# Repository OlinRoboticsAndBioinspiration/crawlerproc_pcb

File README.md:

crawlerproc-pcb
===============

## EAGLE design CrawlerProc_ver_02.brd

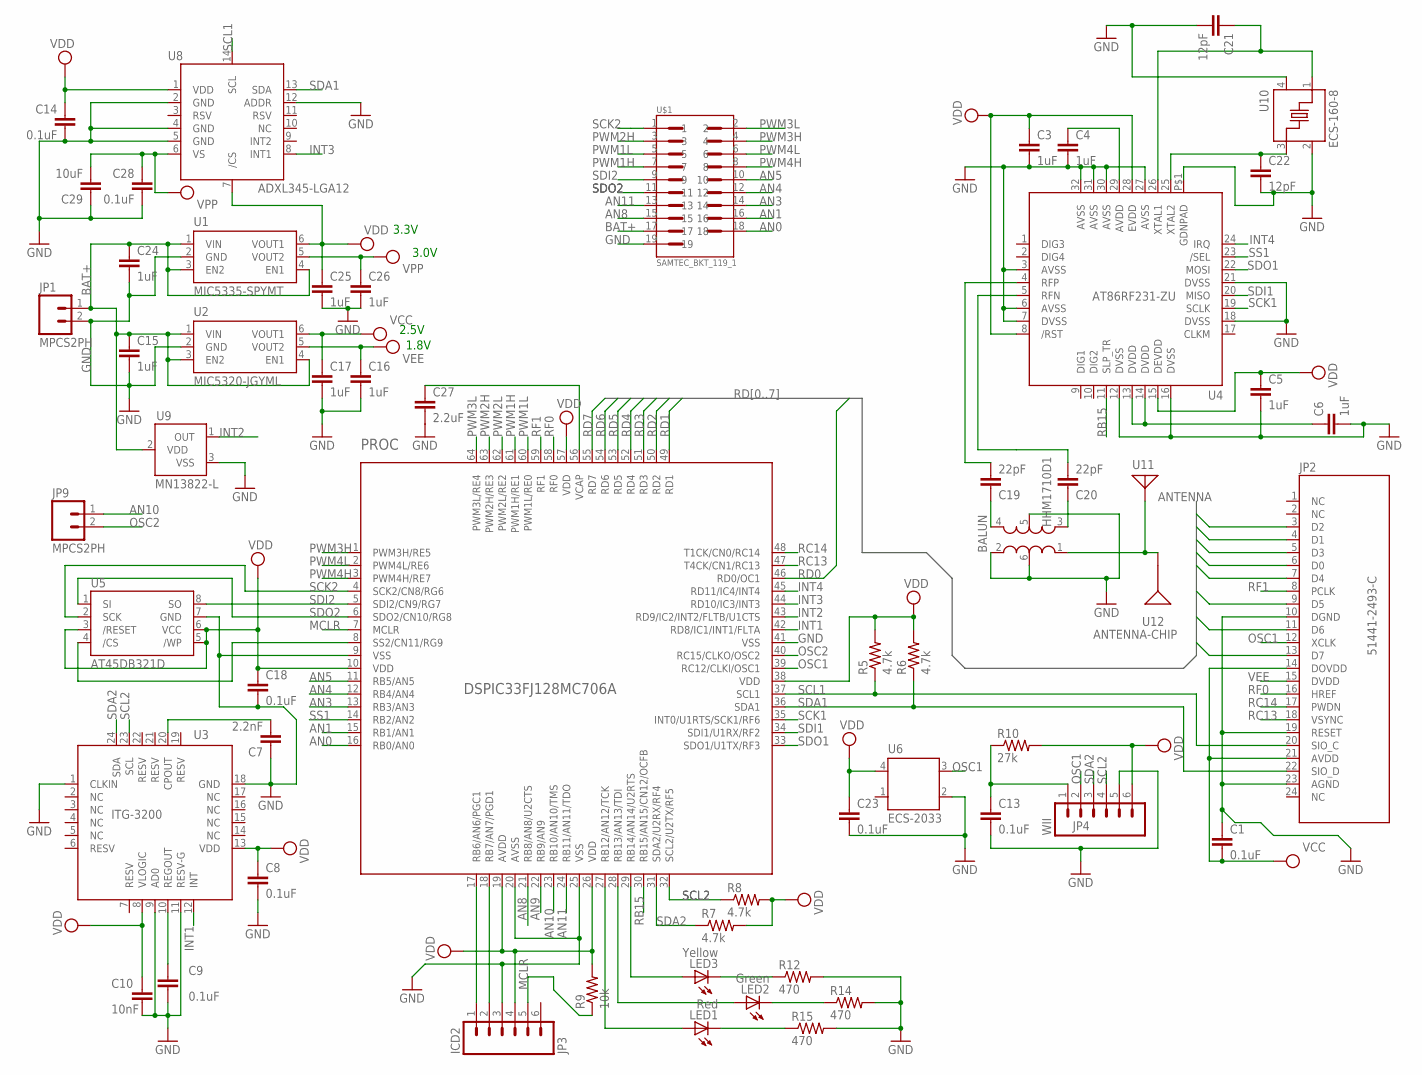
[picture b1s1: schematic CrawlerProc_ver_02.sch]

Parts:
BALUN: HHM1710D1; BALUN
C1, C8, C9, C13, C14, C18, C23, C28: 0.1uF; 0402-CAP
C3, C4, C5, C6, C15, C16, C17, C24, C25, C26: 1uF; 0402-CAP
C7: 2.2nF; 0402-CAP
C10: 10nF; 0402-CAP
C19, C20: 22pF; 0402-CAP
C21, C22: 12pF; 0402-CAP
C27: 2.2uF; 0402-CAP
C29: 10uF; 0603-CAP
JP1, JP9: MPCS2PH; MOLEX-PICO_CLASP_S2P
JP2: 51441-2493-C; MOLEX-52740-2490
JP3: ICD2; MOLEX-PICO_CLASP_S6P
JP4: WII; MOLEX-PICO_CLASP_S6P
LED1: Red; CHIP-LED0603
LED2: Green; CHIP-LED0603
LED3: Yellow; CHIP-LED0603
PROC: DSPIC33FJ128MC706A; TQFP64
R5, R6, R7, R8: 4.7k; R0402
R9: 10k; R0402
R10: 27k; R0402
R12, R14, R15: 470; R0402
U1: MIC5335-SPYMT; MLF-6
U2: MIC5320-JGYML; MLF-6
U3: ITG-3200; QFN-24
U4: AT86RF231-ZU; QFN-32
U5: AT45DB321D; MLF(VDFN)-8
U6: ECS-2033; OSCILLATOR-SMD
U8: ADXL345-LGA12; LGA14
U9: MN13822-L; SOT-23-3
U10: ECS-160-8; CRYSTAL-SMD
U11: ANTENNA; ANTENNA_PAD
U12: ANTENNA-CHIP
U$1: SAMTEC_BKT_119_1; SAMTEC_19P_1MM_MICRO_CONN

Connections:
AN0: PROC.16 (RB0/AN0), U$1.18
AN1: PROC.15 (RB1/AN1), U$1.16
AN3: PROC.13 (RB3/AN3), U$1.14
AN4: PROC.12 (RB4/AN4), U$1.12
AN5: PROC.11 (RB5/AN5), U$1.10
AN8: PROC.21 (RB8/AN8/U2CTS), U$1.15
AN9: PROC.22 (RB9/AN9)
AN10: JP9.1, PROC.23 (RB10/AN10/TMS)
AN11: PROC.24 (RB11/AN11/TDO), U$1.13
BAT+: C15.1, C24.1, JP1.1, U1.1 (VIN), U1.3 (EN2), U1.4 (EN1), U2.1 (VIN), U2.3 (EN2), U2.4 (EN1), U9.2 (VDD), U$1.17
GND: BALUN.2 (RFGND), BALUN.5 (GND), BALUN.6 (NC), C1.1, C3.2, C4.2, C5.2, C6.2, C7.1, C8.2, C9.2, C10.2, C13.2, C14.2, C15.2, C16.2, C17.2, C18.2, C21.2, C22.2, C23.2, C24.2, C25.2, C26.2, C27.2, C28.2, C29.1, JP1.2, JP2.10 (DGND), JP2.19 (RESET), JP2.23 (AGND), JP3.3, JP4.5, PROC.9 (VSS), PROC.20 (AVSS), PROC.25 (VSS), PROC.41 (VSS), R12.2, R14.2, R15.2, U1.2 (GND), U2.2 (GND), U3.1 (CLKIN), U3.9 (AD0), U3.11 (RESV-G), U3.18 (GND), U4.3 (AVSS), U4.6 (AVSS), U4.7 (DVSS), U4.12 (DVSS), U4.16 (DVSS), U4.18 (DVSS), U4.21 (DVSS), U4.27 (AVSS), U4.30 (AVSS), U4.31 (AVSS), U4.32 (AVSS), U4.P$1 (GDNPAD), U5.7 (GND), U6.2 (GND), U8.2 (GND), U8.4 (GND), U8.5 (GND), U8.12 (ADDR), U9.3 (VSS), U10.2 (GND), U10.4 (GND), U$1.19
INT1: PROC.42 (RD8/IC1/INT1/FLTA), U3.12 (INT)
INT2: PROC.43 (RD9/IC2/INT2/FLTB/U1CTS), U9.1 (OUT)
INT3: PROC.44 (RD10/IC3/INT3), U8.8 (INT1)
INT4: PROC.45 (RD11/IC4/INT4), U4.24 (IRQ)
MCLR: JP3.5, PROC.7 (MCLR), R9.1
unnamed: C27.1, PROC.56 (VCAP)
unnamed: LED3.C, R12.1
unnamed: LED3.A, PROC.29 (RB14/AN14/U2RTS)
unnamed: LED2.C, R14.1
unnamed: LED1.C, R15.1
unnamed: LED2.A, PROC.28 (RB13/AN13/TDI)
unnamed: LED1.A, PROC.27 (RB12/AN12/TCK)
unnamed: JP3.1, PROC.17 (RB6/AN6/PGC1)
unnamed: C4.1, U4.29 (AVDD)
unnamed: JP3.2, PROC.18 (RB7/AN7/PGD1)
unnamed: C6.1, U4.13 (DVDD), U4.14 (DVDD)
unnamed: C7.2, U3.20 (CPOUT)
unnamed: C9.1, U3.10 (REGOUT)
unnamed: BALUN.4 (BAL4), C19.1
unnamed: BALUN.3 (BAL3), C20.1
unnamed: C19.2, U4.4 (RFP)
unnamed: PROC.8 (SS2/CN11/RG9), U5.4 (/CS)
unnamed: C20.2, U4.5 (RFN)
unnamed: C22.1, U4.25 (XTAL2), U10.3 (IN/OUT)
unnamed: C21.1, U4.26 (XTAL1), U10.1 (IN/OUT)
unnamed: BALUN.1 (UNBAL), U11.P$1, U12.SIG
unnamed: C13.1, JP4.1, R10.1
OSC1: JP2.12 (XCLK), JP4.2, PROC.39 (RC12/CLKI/OSC1), U6.3 (OUT)
OSC2: JP9.2, PROC.40 (RC15/CLKO/OSC2)
PWM1H: PROC.61 (PWM1H/RE1), U$1.7
PWM1L: PROC.60 (PWM1L/RE0), U$1.5
PWM2H: PROC.63 (PWM2H/RE3), U$1.3
PWM2L: PROC.62 (PWM2L/RE2)
PWM3H: PROC.1 (PWM3H/RE5), U$1.4
PWM3L: PROC.64 (PWM3L/RE4), U$1.2
PWM4H: PROC.3 (PWM4H/RE7), U$1.8
PWM4L: PROC.2 (PWM4L/RE6), U$1.6
RB15: PROC.30 (RB15/AN15/CN12/OCFB), U4.11 (SLP_TR)
RC13: JP2.18 (VSYNC), PROC.47 (T4CK/CN1/RC13)
RC14: JP2.17 (PWDN), PROC.48 (T1CK/CN0/RC14)
RD0: JP2.6 (D0), PROC.46 (RD0/OC1)
RD1: JP2.4 (D1), PROC.49 (RD1)
RD2: JP2.3 (D2), PROC.50 (RD2)
RD3: JP2.5 (D3), PROC.51 (RD3)
RD4: JP2.7 (D4), PROC.52 (RD4)
RD5: JP2.9 (D5), PROC.53 (RD5)
RD6: JP2.11 (D6), PROC.54 (RD6)
RD7: JP2.13 (D7), PROC.55 (RD7)
RF0: JP2.16 (HREF), PROC.58 (RF0)
RF1: JP2.8 (PCLK), PROC.59 (RF1)
SCK1: PROC.35 (INT0/U1RTS/SCK1/RF6), U4.19 (SCLK)
SCK2: PROC.4 (SCK2/CN8/RG6), U5.2 (SCK), U$1.1
SCL1: JP2.20 (SIO_C), PROC.37 (SCL1), R5.1, U8.14 (SCL)
SCL2: JP4.4, PROC.32 (SCL2/U2TX/RF5), R8.1, U3.23 (SCL)
SDA1: JP2.22 (SIO_D), PROC.36 (SDA1), R6.1, U8.13 (SDA)
SDA2: JP4.3, PROC.31 (SDA2/U2RX/RF4), R7.1, U3.24 (SDA)
SDI1: PROC.34 (SDI1/U1RX/RF2), U4.20 (MISO)
SDI2: PROC.5 (SDI2/CN9/RG7), U5.8 (SO), U$1.9
SDO1: PROC.33 (SDO1/U1TX/RF3), U4.22 (MOSI)
SDO2: PROC.6 (SDO2/CN10/RG8), U5.1 (SI), U$1.11
SS1: PROC.14 (RB2/AN2), U4.23 (/SEL)
VCC: C1.2, C17.1, JP2.14 (DOVDD), JP2.21 (AVDD), U2.6 (VOUT1)
VDD: C3.1, C5.1, C8.1, C10.1, C14.1, C18.1, C23.1, C25.1, JP3.4, JP4.6, PROC.10 (VDD), PROC.19 (AVDD), PROC.26 (VDD), PROC.38 (VDD), PROC.57 (VDD), R5.2, R6.2, R7.2, R8.2, R9.2, R10.2, U1.6 (VOUT1), U3.8 (VLOGIC), U3.13 (VDD), U4.8 (/RST), U4.15 (DEVDD), U4.28 (EVDD), U5.3 (/RESET), U5.5 (/WP), U5.6 (VCC), U6.4 (VDD), U8.1 (VDD), U8.7 (/CS)
VEE: C16.1, JP2.15 (DVDD), U2.5 (VOUT2)
VPP: C26.1, C28.1, C29.2, U1.5 (VOUT2), U8.6 (VS)

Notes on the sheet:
3.3V
2.5V
1.8V
3.0V

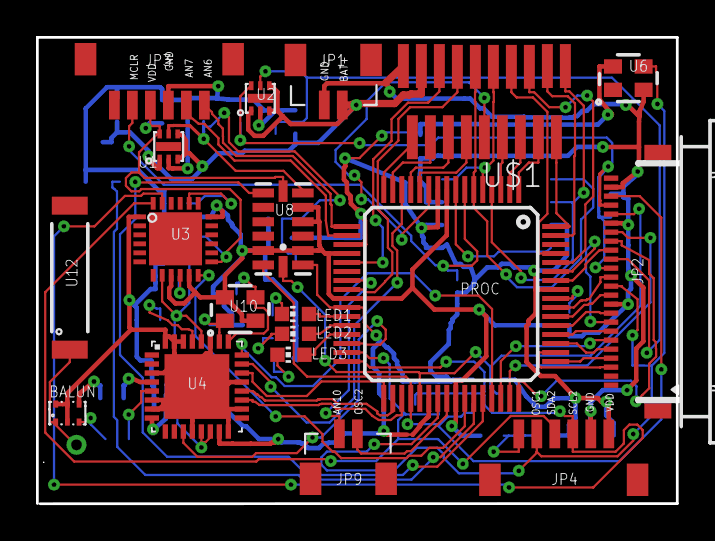
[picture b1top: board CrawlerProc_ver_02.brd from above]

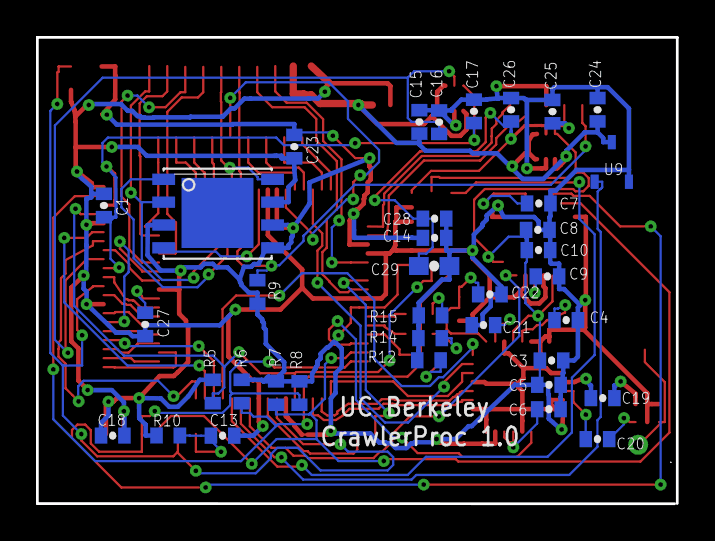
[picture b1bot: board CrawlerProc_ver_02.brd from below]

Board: 2 copper layers, 35.6 x 25.9 mm, 57 parts (37 on the bottom side), 74 nets.

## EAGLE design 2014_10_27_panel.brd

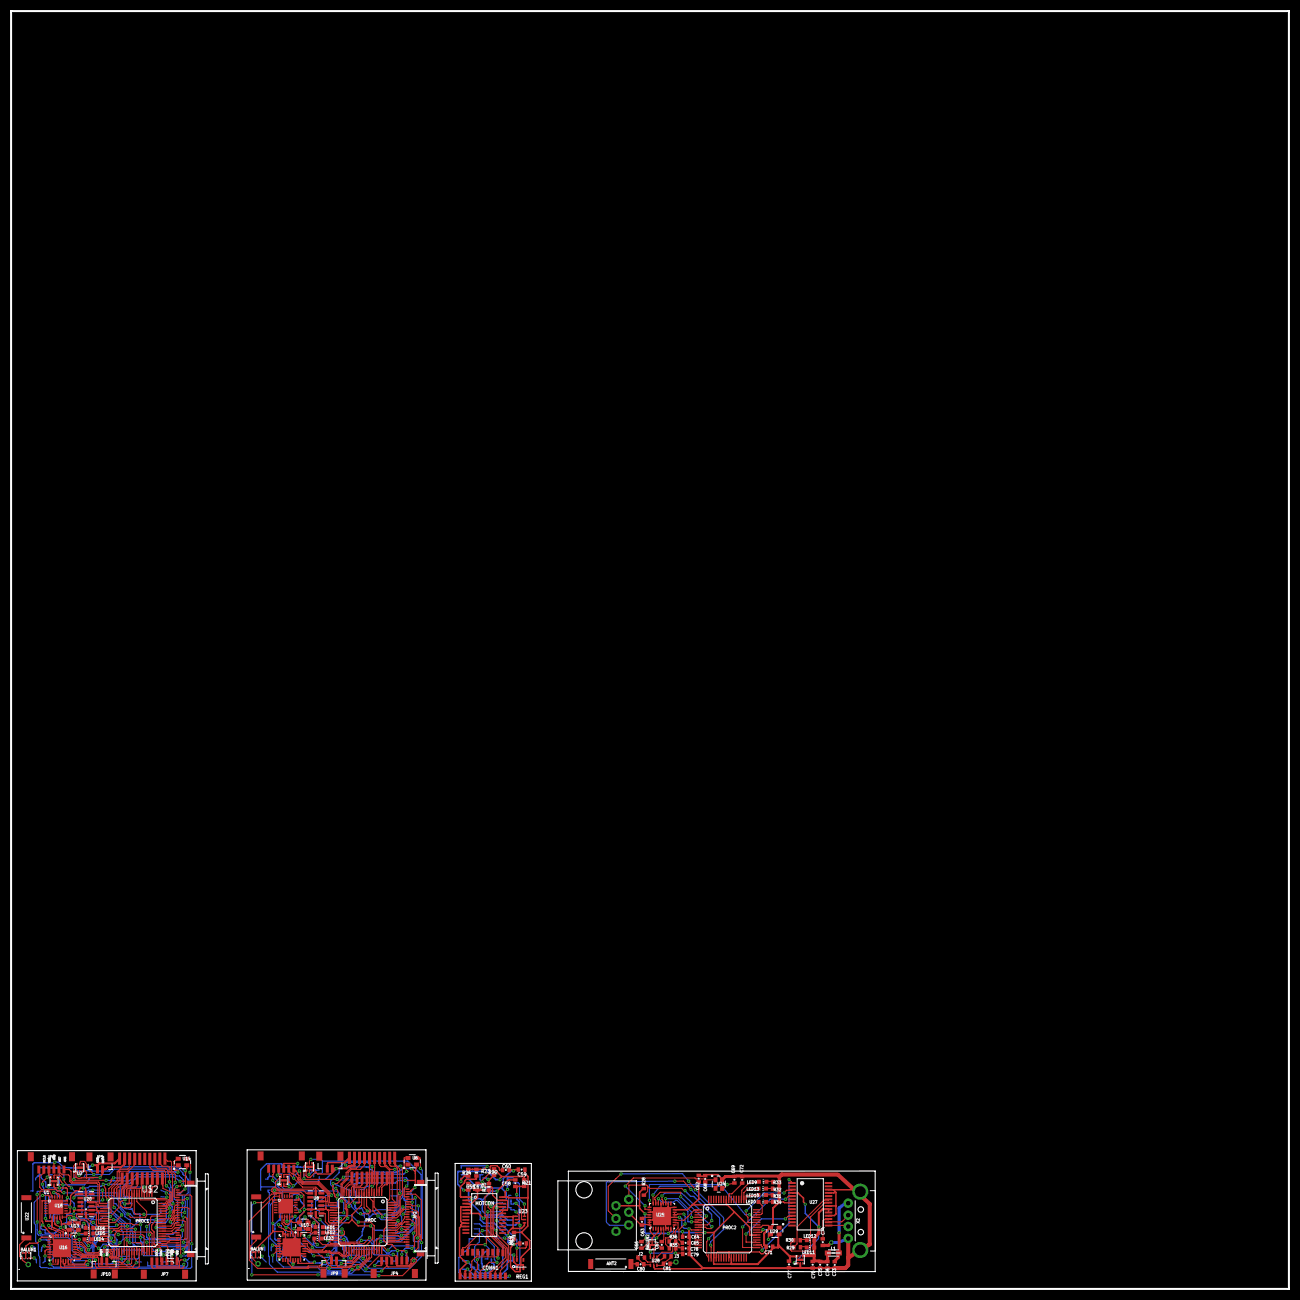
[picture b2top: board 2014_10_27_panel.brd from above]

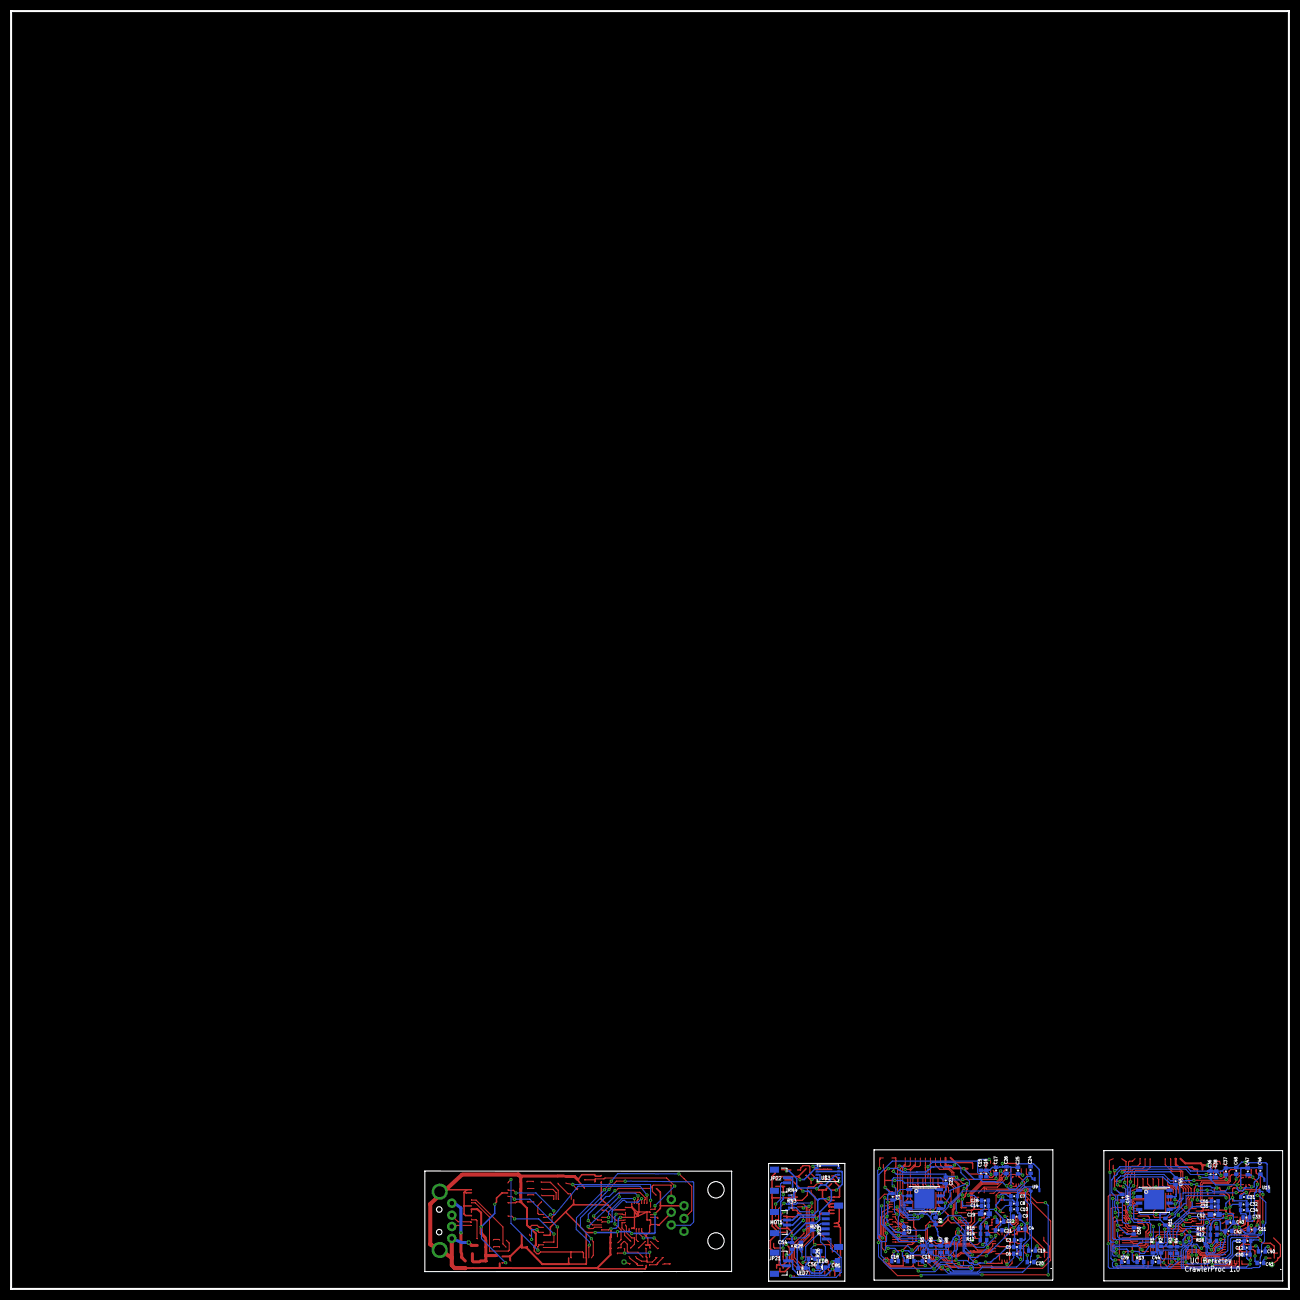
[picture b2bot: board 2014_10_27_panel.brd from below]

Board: 2 copper layers, 254.0 x 254.0 mm, 195 parts (89 on the bottom side), 228 nets.

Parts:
ANT1: ANTENNA; ANTENNA_PAD
ANT2: ANTENNA-CHIP
BALUN, BALUN1, BALUN2: HHM1710D1; BALUN
C1, C8, C9, C13, C14, C18, C23, C28, C32, C33, C35, C39, C44, C45, C49, C51, C57, C58, C59, C60, C74, C75, C77: 0.1uF; 0402-CAP
C2, C3, C4, C5, C6, C11, C12, C15, C16, C17, C24, C25, C26, C30, C36, C37, C38, C46, C47, C48, C53, C62, C63, C64, C65, C70, C71: 1uF; 0402-CAP
C7, C31: 2.2nF; 0402-CAP
C10, C34, C73: 10nF; 0402-CAP
C19, C20, C40, C41, C66, C67, C78, C79, C80, C81: 22pF; 0402-CAP
C21, C22, C42, C43, C68, C69: 12pF; 0402-CAP
C27, C50, C54, C72: 2.2uF; 0402-CAP
C29, C52, C61: 10uF; 0603-CAP
C55: 0.01uF; 0402-CAP
C56: 1nF; 0402-CAP
C76: 4.7uF; 0402-CAP
CONN1: SAMTEC_BKS_119_1; SAMTEC_19P_1MM_SOCKET
J1: RJ11-6PTH; RJ11-6
J2, J3: 0; R0402
JP1, JP5, JP9, JP10, JP21, JP22: MPCS2PH; MOLEX-PICO_CLASP_S2P
JP2, JP8: 51441-2493-C; MOLEX-52740-2490
JP3, JP6: ICD2; MOLEX-PICO_CLASP_S6P
JP4, JP7: WII; MOLEX-PICO_CLASP_S6P
JP23: MPCS6PH; MOLEX-PICO_CLASP_S6P
L1: Ferrite Bead; 0805
LED0, LED1, LED6: Red; CHIP-LED0603
LED2, LED5, LED10, LED11: Green; CHIP-LED0603
LED3, LED4, LED13: Yellow; CHIP-LED0603
LED7: Green; LED-0603
LED8: Red; LED-0603
LED9: Blue; CHIP-LED0603
LED12: Orange; CHIP-LED0603
MOT1: MPCS2PH; MOLEX-PICO_CLASP_S2P
MOTCON: TB6621FNG; SSOP24
PROC, PROC1: DSPIC33FJ128MC706A; TQFP64
PROC2: DSPIC33; TQFP64
R1, R2, R3, R4, R5, R6, R7, R8: 4.7k; R0402
R9, R11, R28: 10k; R0402
R10, R13: 27k; R0402
R12, R14, R15, R16, R17, R18, R29, R30, R31, R32, R33, R34: 470; R0402
R19, R20: 100K; 0402-RES
R21, R23: 15K; 0402-RES
R22, R24: 12K; 0402-RES
R25: 1K; 0402-RES
R26, R27: 470; 0402-RES
R35, R36: 2K; R0402
REG1: ZXCL330H5TA; SC-70-5
RN3: 1K; EXB24V
RN4: 100K; EXB24V
U1, U19, U26: MIC5335-SPYMT; MLF-6
U2, U17: MIC5320-JGYML; MLF-6
U3, U18: ITG-3200; QFN-24
U4, U16, U25: AT86RF231-ZU; QFN-32
U5, U7: AT45DB321D; MLF(VDFN)-8
U6, U14, U29: ECS-2033; OSCILLATOR-SMD
U8, U20: ADXL345-LGA12; LGA14
U9, U15: MN13822-L; SOT-23-3
U10, U13: ECS-160-8; CRYSTAL-SMD
U11, U21: ANTENNA; ANTENNA_PAD
U12, U22: ANTENNA-CHIP
U23: SI1988DHA; SC-70-6
U24: ECX-2236; CRYSTAL-SMD
U27: FT232RL; SSOP28
U28: AS183-92; SC-70-6
U$1, U$2: SAMTEC_BKT_119_1; SAMTEC_19P_1MM_MICRO_CONN
U$3: LTC1992; 8-PIN_MSOP
X2: USB-A-H

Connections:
AN0: PROC.16, U$1.18
AN1: PROC.15, U$1.16
AN2: PROC1.24, U$2.13
AN3: PROC.13, U$1.14
AN4: PROC.12, U$1.12
AN5: PROC.11, U$1.10
AN6: PROC1.15, U$2.16
AN7: PROC1.16, U$2.18
AN8: PROC.21, U$1.15
AN10: JP9.1, PROC.23
AN11: PROC.24, U$1.13
AN12: PROC1.13, U$2.14
AN13: PROC1.12, U$2.12
AN14: PROC1.11, U$2.10
AN15: JP10.1, PROC1.23
AN16: PROC1.21, U$2.15
AN18: C56.2, CONN1.4, R25.2
AN22: CONN1.5, R27.2
AN23: CONN1.7, R26.2
AN24: CONN1.2, R19.2, R20.1
BAT+: C15.1, C24.1, JP1.1, U1.1, U1.3, U1.4, U2.1, U2.3, U2.4, U9.2, U$1.17
BAT+1: C36.1, C46.1, JP5.1, U15.2, U17.1, U17.3, U17.4, U19.1, U19.3, U19.4, U$2.17
GND: BALUN.2, BALUN.5, BALUN.6, C1.1, C3.2, C4.2, C5.2, C6.2, C7.1, C8.2, C9.2, C10.2, C13.2, C14.2, C15.2, C16.2, C17.2, C18.2, C21.2, C22.2, C23.2, C24.2, C25.2, C26.2, C27.2, C28.2, C29.1, JP1.2, JP2.10, JP2.19, JP2.23, JP3.3, JP4.5, PROC.9, PROC.20, PROC.25, PROC.41, R12.2, R14.2, R15.2, U1.2, U2.2, U3.1, U3.9, U3.11, U3.18, U4.3, U4.6, U4.7, U4.12, U4.16, U4.18, U4.21, U4.27, U4.30, U4.31, U4.32, U4.P$1, U5.7, U6.2, U8.2, U8.4, U8.5, U8.12, U9.3, U10.2, U10.4, U$1.19
GND1: BALUN1.2, BALUN1.5, BALUN1.6, C2.2, C11.2, C12.2, C30.2, C31.1, C32.2, C33.2, C34.2, C35.2, C36.2, C37.2, C38.2, C39.2, C42.2, C43.2, C44.2, C45.2, C46.2, C47.2, C48.2, C49.1, C50.2, C51.2, C52.1, JP5.2, JP6.3, JP7.5, JP8.10, JP8.19, JP8.23, PROC1.9, PROC1.20, PROC1.25, PROC1.41, R16.2, R17.2, R18.2, U7.7, U13.2, U13.4, U14.2, U15.3, U16.3, U16.6, U16.7, U16.12, U16.16, U16.18, U16.21, U16.27, U16.30, U16.31, U16.32, U16.P$1, U17.2, U18.1, U18.9, U18.11, U18.18, U19.2, U20.2, U20.4, U20.5, U20.12, U$2.19
GND2: C53.1, C54.1, C55.1, C56.1, C57.1, C59.1, C60.1, C61.1, CONN1.1, LED7.C, LED8.C, MOTCON.3, MOTCON.4, MOTCON.9, MOTCON.10, MOTCON.18, R20.2, REG1.2, RN4.1, RN4.2, U23.1, U23.4, U$3.6
GND3: BALUN2.2, BALUN2.5, BALUN2.6, C62.2, C63.2, C64.2, C65.2, C68.2, C69.2, C70.2, C71.2, C72.2, C73.1, C74.1, C75.1, C76.1, C77.2, C78.1, C79.1, J1.3, PROC2.9, PROC2.20, PROC2.25, PROC2.41, R31.1, R32.1, R33.1, R34.1, U24.2, U24.4, U25.3, U25.6, U25.7, U25.12, U25.16, U25.18, U25.21, U25.27, U25.30, U25.31, U25.32, U25.P$1, U26.2, U27.7, U27.18, U27.21, U27.25, U27.26, U28.2, U29.2, X2.GND
INT1: PROC.42, U3.12
INT2: PROC.43, U9.1
INT3: PROC.44, U8.8
INT4: PROC.45, U4.24
INT5: PROC1.42, U18.12
INT6: PROC1.43, U15.1
INT7: PROC1.44, U20.8
INT8: PROC1.45, U16.24
INT9: PROC2.45, U25.24
MCLR: JP3.5, PROC.7, R9.1
MCLR1: JP6.5, PROC1.7, R11.1
MCLR2: J1.1, PROC2.7, R28.1
unnamed: C27.1, PROC.56
unnamed: C11.1, U16.29
unnamed: LED3.C, R12.1
unnamed: C30.1, U16.13, U16.14
unnamed: C31.2, U18.20
unnamed: LED3.A, PROC.29
unnamed: LED2.C, R14.1
unnamed: LED1.C, R15.1
unnamed: LED2.A, PROC.28
unnamed: C33.1, U18.10
unnamed: LED1.A, PROC.27
unnamed: PROC1.8, U7.4
unnamed: BALUN1.4, C40.1
unnamed: BALUN1.3, C41.1
unnamed: C40.2, U16.4
unnamed: C41.2, U16.5
unnamed: BALUN1.1, U21.P$1, U22.SIG
unnamed: C43.1, U13.3, U16.25
unnamed: C42.1, U13.1, U16.26
unnamed: C44.1, JP7.1, R13.1
unnamed: JP3.1, PROC.17
unnamed: PROC1.6, U7.1
unnamed: C4.1, U4.29
unnamed: JP3.2, PROC.18
unnamed: LED4.C, R16.1
unnamed: LED4.A, PROC1.29
unnamed: JP6.1, PROC1.17
unnamed: C6.1, U4.13, U4.14
unnamed: C7.2, U3.20
unnamed: JP6.2, PROC1.18
unnamed: LED5.C, R17.1
unnamed: C9.1, U3.10
unnamed: LED6.C, R18.1
unnamed: LED5.A, PROC1.28
unnamed: LED6.A, PROC1.27
unnamed: C50.1, PROC1.56
unnamed: JP22.2, U23.6
unnamed: JP21.2, U23.3
unnamed: RN3.3, RN4.4, U23.5
unnamed: R21.2, R22.1, U$3.1
unnamed: R23.2, R24.1, U$3.8
unnamed: PROC1.4, U7.2
unnamed: BALUN.4, C19.1
unnamed: R24.2, U$3.5
unnamed: PROC1.5, U7.8
unnamed: BALUN.3, C20.1
unnamed: C19.2, U4.4
unnamed: PROC.8, U5.4
unnamed: C20.2, U4.5
unnamed: C22.1, U4.25, U10.3
unnamed: C21.1, U4.26, U10.1
unnamed: BALUN.1, U11.P$1, U12.SIG
unnamed: C55.2, U$3.2, U$3.7
unnamed: R22.2, R25.1, U$3.4
unnamed: RN3.4, RN4.3, U23.2
unnamed: LED7.A, R27.1
unnamed: C13.1, JP4.1, R10.1
unnamed: LED8.A, R26.1
unnamed: C63.1, U25.29
unnamed: C65.1, U25.13, U25.14
unnamed: BALUN2.4, C66.1
unnamed: BALUN2.3, C67.1
unnamed: C66.2, U25.4
unnamed: C67.2, U25.5
unnamed: C69.1, U24.3, U25.25
unnamed: C68.1, U24.1, U25.26
unnamed: C72.1, PROC2.56
unnamed: C73.2, L1.1, X2.VBUS
unnamed: U27.16, X2.D-
unnamed: U27.15, X2.D+
unnamed: C74.2, U27.17
unnamed: R36.1, U25.10
unnamed: R35.1, U25.9
unnamed: C81.1, J3.2, U28.3
unnamed: C80.2, J2.2, U28.1
unnamed: LED10.A, PROC2.49
unnamed: LED9.A, PROC2.51
unnamed: LED10.C, R31.2
unnamed: LED13.A, PROC2.50
unnamed: LED13.C, R32.2
unnamed: LED9.C, R33.2
unnamed: LED0.A, PROC2.46
unnamed: LED0.C, R34.2
unnamed: J1.5, PROC2.17
unnamed: J1.4, PROC2.18
unnamed: R29.1, U27.23
unnamed: R30.1, U27.22
unnamed: LED11.C, R29.2
unnamed: LED12.C, R30.2
unnamed: C78.2, R36.2, U28.4
unnamed: C79.2, R35.2, U28.6
unnamed: BALUN2.1, J2.1, J3.1, U28.5
unnamed: ANT2.SIG, C80.1
unnamed: ANT1.P$1, C81.2
OSC1: JP2.12, JP4.2, PROC.39, U6.3
OSC2: JP9.2, PROC.40
OSC3: JP7.2, JP8.12, PROC1.39, U14.3
OSC4: JP10.2, PROC1.40
OSC5: PROC2.39, U29.3
PWM1H: PROC.61, U$1.7
PWM1H1: PROC1.61, U$2.7
PWM1H2: CONN1.13, MOTCON.21
PWM1L: PROC.60, U$1.5
PWM1L1: PROC1.60, U$2.5
PWM1L2: CONN1.15, MOTCON.22
PWM2H: PROC.63, U$1.3
PWM2H1: PROC1.63, U$2.3
PWM2H2: CONN1.17, JP23.4
PWM2L: PROC1.62, U$2.1
PWM3H: PROC.1, U$1.4
PWM3H1: PROC1.1, U$2.4
PWM3H2: CONN1.16, RN3.1
PWM3L: PROC.64, U$1.2
PWM3L1: PROC1.64, U$2.2
PWM3L2: CONN1.18, RN3.2
PWM4H: PROC.3, U$1.8
PWM4H1: PROC1.3, U$2.8
PWM4L: PROC.2, U$1.6
PWM4L1: PROC1.2, U$2.6
RB1: PROC1.30, U16.11
RB15: PROC.30, U4.11
RC1: JP8.18, PROC1.47
RC2: JP8.17, PROC1.48
RC13: JP2.18, PROC.47
RC14: JP2.17, PROC.48
RD0: JP2.6, PROC.46
RD1: JP2.4, PROC.49
RD2: JP2.3, PROC.50
RD3: JP2.5, PROC.51
RD4: JP2.7, PROC.52
RD5: JP2.9, PROC.53
RD6: JP2.11, PROC.54
RD7: JP2.13, PROC.55
RD8: JP8.3, PROC1.50
RD9: JP8.5, PROC1.51
RD10: JP8.6, PROC1.46
RD11: JP8.7, PROC1.52
RD12: JP8.9, PROC1.53
RD13: JP8.11, PROC1.54
RD14: JP8.13, PROC1.55
RD15: JP8.4, PROC1.49
RE5: PROC2.1, U25.11
RF0: JP2.16, PROC.58
RF1: JP2.8, PROC.59
RF2: JP8.8, PROC1.59
RF3: JP8.16, PROC1.58
SCK1: PROC.35, U4.19
SCK2: PROC.4, PROC.62, U5.2, U$1.1
SCK3: PROC1.35, U16.19
SCK4: CONN1.19, JP23.1
SCK5: PROC2.4, U25.19
SCL1: JP2.20, PROC.37, R5.1, U8.14
SCL2: JP4.4, PROC.32, R8.1, U3.23
SCL3: JP8.20, PROC1.37, R1.1, U20.14
SCL4: JP7.4, PROC1.32, R4.1, U18.23
SDA1: JP2.22, PROC.36, R6.1, U8.13
SDA2: JP4.3, PROC.31, R7.1, U3.24
SDA3: JP8.22, PROC1.36, R2.1, U20.13
SDA4: JP7.3, PROC1.31, R3.1, U18.24
SDI1: PROC.34, U4.20
SDI2: PROC.5, U5.8, U$1.9
SDI3: PROC1.34, U16.20
SDI4: CONN1.11, JP23.2
SDI5: PROC2.5, U25.20
SDO1: PROC.33, U4.22
SDO2: PROC.6, U5.1, U$1.11
SDO3: PROC1.33, U16.22
SDO4: CONN1.9, JP23.3
SDO5: PROC2.6, U25.22
SS1: PROC.14, U4.23
SS2: PROC1.14, U16.23
SS3: PROC2.8, U25.23
U1CTS: PROC2.43, U27.3
U1RTS: PROC2.35, U27.11
U1RX: PROC2.34, U27.1
U1TX: PROC2.33, U27.5
VBAT: C54.2, C59.2, C61.2, CONN1.3, JP21.1, JP22.1, MOTCON.24, R19.1, REG1.1, REG1.3
VCC: C1.2, C17.1, JP2.14, JP2.21, U2.6
VCC1: C37.1, C49.2, JP8.14, JP8.21, U17.6
VCC2: C53.2, C57.2, C60.2, MOTCON.19, MOTCON.20, MOTCON.23, REG1.5, U$3.3
VDD: C3.1, C5.1, C8.1, C10.1, C14.1, C18.1, C23.1, C25.1, JP3.4, JP4.6, PROC.10, PROC.19, PROC.26, PROC.38, PROC.57, R5.2, R6.2, R7.2, R8.2, R9.2, R10.2, U1.6, U3.8, U3.13, U4.8, U4.15, U4.28, U5.3, U5.5, U5.6, U6.4, U8.1, U8.7
VDD1: C2.1, C12.1, C32.1, C34.1, C35.1, C39.1, C45.1, C47.1, JP6.4, JP7.6, PROC1.10, PROC1.19, PROC1.26, PROC1.38, PROC1.57, R1.2, R2.2, R3.2, R4.2, R11.2, R13.2, U7.3, U7.5, U7.6, U14.4, U16.8, U16.15, U16.28, U18.8, U18.13, U19.6, U20.1, U20.7
VDD2: C62.1, C64.1, C71.1, C77.1, J1.2, PROC2.10, PROC2.19, PROC2.26, PROC2.38, PROC2.57, R28.2, U25.8, U25.15, U25.28, U26.6, U29.4
VEE: C16.1, JP2.15, U2.5
VEE1: C38.1, JP8.15, U17.5
VM1+: C58.1, MOT1.2, MOTCON.5, MOTCON.6, R21.1
VM1-: C58.2, MOT1.1, MOTCON.1, MOTCON.2, R23.1
VPP: C26.1, C28.1, C29.2, U1.5, U8.6
VPP1: C48.1, C51.1, C52.2, U19.5, U20.6
VPP2: C70.1, C75.2, C76.2, L1.2, LED11.A, LED12.A, U26.1, U26.4, U27.4, U27.19, U27.20

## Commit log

2013-10-17 added CrawlerProc board files
2014-10-09 Added AMH.lbr
2014-10-15 Mechanical pad updates for 6 pin I2C connector and other 2 pin connector on that side
2014-10-15 Added stan.lbr Eagle library
2014-10-22 Revert "Added stan.lbr Eagle library"
    This reverts commit 958928f18762e6a440f7f5cd493e03dd5501e82c.
2014-10-22 Added dimensions
2014-10-22 Change 02 Schematic to have SPI pinout
2014-10-22 added Freerouter dsn
2014-10-22 Updated with routing for SPI breakout
2014-10-23 SPI breakout routing changes and Freerouter script
2014-10-27 Added beginnings of panelized board
2014-10-29 Updates to fully routed crawlerproc
2015-02-13 Fixed error that connected PWM2L to the SCK2 line
